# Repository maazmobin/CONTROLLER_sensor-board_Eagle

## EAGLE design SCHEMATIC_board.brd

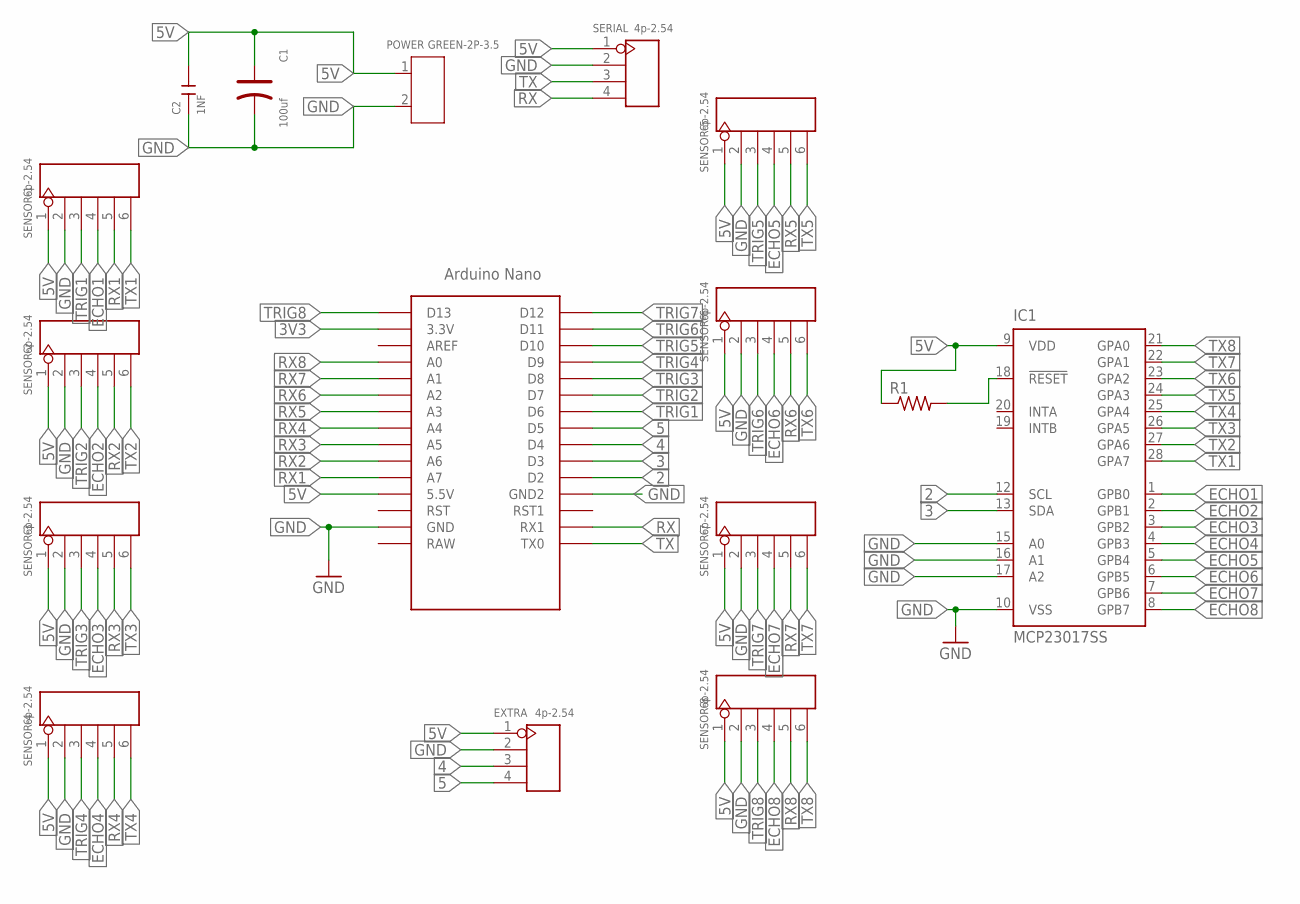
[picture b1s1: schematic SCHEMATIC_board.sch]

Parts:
C1: 100uf; PC-D5.3MM
C2: 1NF; C1206
EXTRA: 4p-2.54; H4-2.54
IC1: MCP23017SS; SSOP28
POWER: GREEN-2P-3.5; H2-3.5-7.0X7.0MM
R1: R-US_M1206; M1206
SENSOR-1, SENSOR-2, SENSOR-3, SENSOR-4, SENSOR-5, SENSOR-6, SENSOR-7, SENSOR-8: 6p-2.54; H6-2.54
SERIAL: 4p-2.54; H4-2.54
U$1: NANO

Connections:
2: IC1.12 (SCL), U$1.D2
3: IC1.13 (SDA), U$1.D3
3V3: U$1.3.3V
4: EXTRA.3, U$1.D4
5: EXTRA.4, U$1.D5
5V: C1.+, C2.2, EXTRA.1, IC1.9 (VDD), POWER.1, R1.1, SENSOR-1.1, SENSOR-2.1, SENSOR-3.1, SENSOR-4.1, SENSOR-5.1, SENSOR-6.1, SENSOR-7.1, SENSOR-8.1, SERIAL.1, U$1.5V (5.5V)
ECHO1: IC1.1 (GPB0), SENSOR-1.4
ECHO2: IC1.2 (GPB1), SENSOR-2.4
ECHO3: IC1.3 (GPB2), SENSOR-3.4
ECHO4: IC1.4 (GPB3), SENSOR-4.4
ECHO5: IC1.5 (GPB4), SENSOR-5.4
ECHO6: IC1.6 (GPB5), SENSOR-6.4
ECHO7: IC1.7 (GPB6), SENSOR-7.4
ECHO8: IC1.8 (GPB7), SENSOR-8.4
GND: C1.-, C2.1, EXTRA.2, IC1.10 (VSS), IC1.15 (A0), IC1.16 (A1), IC1.17 (A2), POWER.2, SENSOR-1.2, SENSOR-2.2, SENSOR-3.2, SENSOR-4.2, SENSOR-5.2, SENSOR-6.2, SENSOR-7.2, SENSOR-8.2, SERIAL.2, U$1.GND, U$1.GND1 (GND2)
unnamed: IC1.18 (!RESET), R1.2
RX: SERIAL.4, U$1.RX1
RX1: SENSOR-1.5, U$1.A7
RX2: SENSOR-2.5, U$1.A6
RX3: SENSOR-3.5, U$1.A5
RX4: SENSOR-4.5, U$1.A4
RX5: SENSOR-5.5, U$1.A3
RX6: SENSOR-6.5, U$1.A2
RX7: SENSOR-7.5, U$1.A1
RX8: SENSOR-8.5, U$1.A0
TRIG1: SENSOR-1.3, U$1.D6
TRIG2: SENSOR-2.3, U$1.D7
TRIG3: SENSOR-3.3, U$1.D8
TRIG4: SENSOR-4.3, U$1.D9
TRIG5: SENSOR-5.3, U$1.D10
TRIG6: SENSOR-6.3, U$1.D11
TRIG7: SENSOR-7.3, U$1.D12
TRIG8: SENSOR-8.3, U$1.D13
TX: SERIAL.3, U$1.TX0
TX1: IC1.28 (GPA7), SENSOR-1.6
TX2: IC1.27 (GPA6), SENSOR-2.6
TX3: IC1.26 (GPA5), SENSOR-3.6
TX4: IC1.25 (GPA4), SENSOR-4.6
TX5: IC1.24 (GPA3), SENSOR-5.6
TX6: IC1.23 (GPA2), SENSOR-6.6
TX7: IC1.22 (GPA1), SENSOR-7.6
TX8: IC1.21 (GPA0), SENSOR-8.6

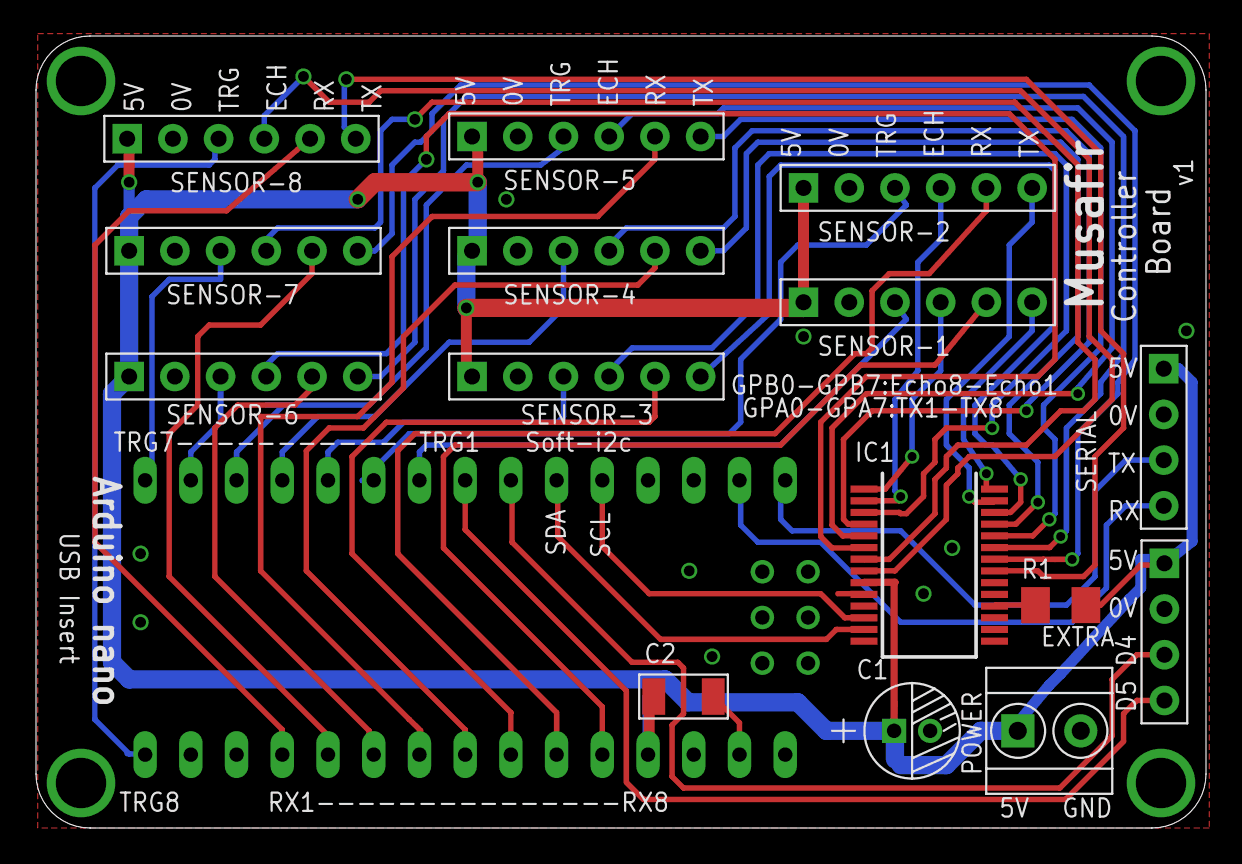
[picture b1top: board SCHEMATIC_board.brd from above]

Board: 2 copper layers, 65.0 x 44.0 mm, 16 parts (0 on the bottom side), 41 nets.

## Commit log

2016-06-30 :octocat: Added .gitattributes & .gitignore files
2016-06-30 Complete schematic_ working on layout
2016-06-30 layout complete
2016-06-30 Layout, silk Completed, Reviewing
    Musafir Controller Board
